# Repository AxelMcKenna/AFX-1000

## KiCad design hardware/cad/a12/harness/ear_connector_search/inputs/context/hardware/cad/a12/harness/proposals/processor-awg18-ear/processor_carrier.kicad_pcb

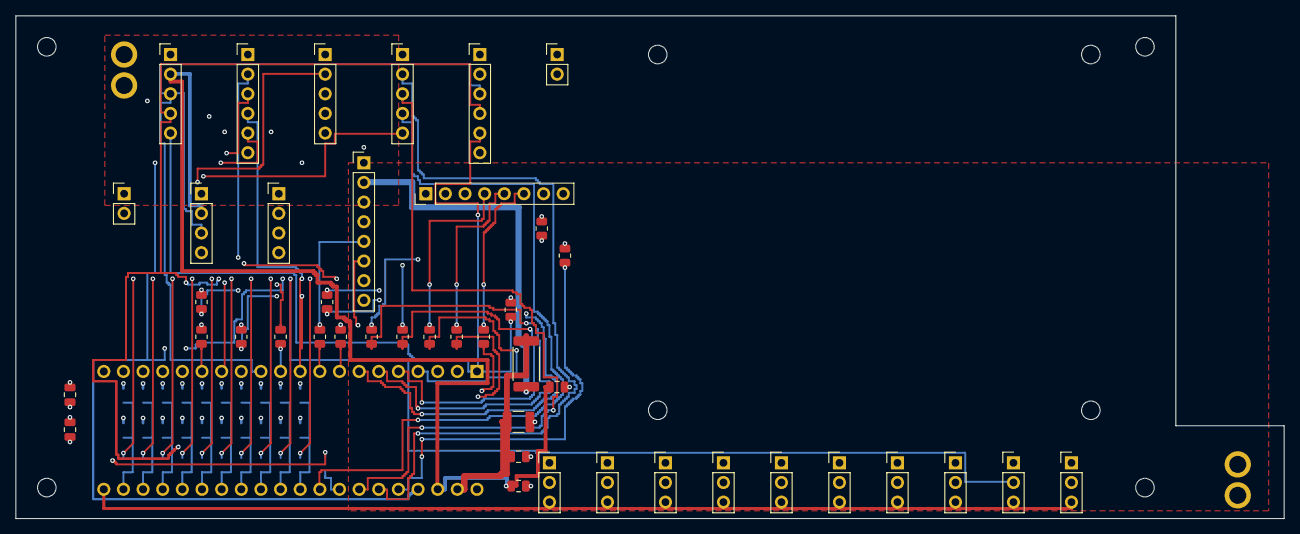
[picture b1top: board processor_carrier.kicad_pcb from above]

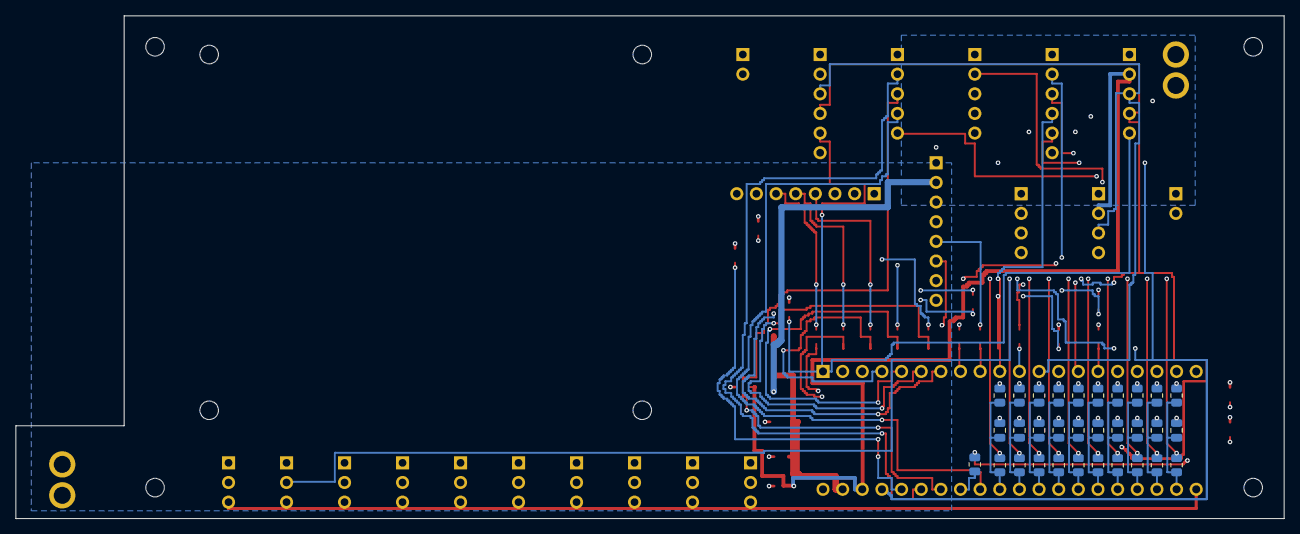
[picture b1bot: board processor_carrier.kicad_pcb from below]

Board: 4 copper layers, 164.0 x 65.0 mm, 85 parts (31 on the bottom side), 61 nets.

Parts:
C1: 22uF 25V X7R; C_1210_3225Metric
C2, C4, C6, C11, C12, C13, C14, C15, C16, C17, C18, C19, C20: 100nF 16V X7R; C_0805_2012Metric
C3: 1uF 16V X7R; C_0805_2012Metric
C5: 4.7uF 16V X7R; C_0805_2012Metric
H1, H2, H3, H4: M2_CLEARANCE; M2_Insert_Clearance
H5, H6, H7, H8: M2_CLEARANCE; M2_Daughter
J1, J13: Alpha6715_AWG18_DIRECT_SOLDER_PROPOSAL; AWG18_Solder_2x1_P4mm_D2p2
J2, J4, J5: Header5; PinHeader_1x05_P2.54mm_Vertical
J3, J6: Header6; PinHeader_1x06_P2.54mm_Vertical
J7, J8: Header2; PinHeader_1x02_P2.54mm_Vertical
J9, J10: Header4; PinHeader_1x04_P2.54mm_Vertical
J11, J12: Header8; PinHeader_1x08_P2.54mm_Vertical
J20, J21, J22, J23, J24, J25, J26, J27, J28, J29: Header3; PinHeader_1x03_P2.54mm_Vertical
R1: 0.47R 1% 1W; R_2512_6332Metric
R2: 10k 1%; R_0805_2012Metric
R3, R4, R5, R6: 100k 1%; R_0805_2012Metric
R10, R11, R12, R13, R14, R15, R16, R17, R18, R19, R20: 33R 1%; R_0805_2012Metric
R31, R32, R33, R34, R35, R36, R37, R38, R39, R40: 1k 1%; R_0805_2012Metric
R41, R42, R43, R44, R45, R46, R47, R48, R49, R50: 1M 1%; R_0805_2012Metric
U1: DaisySeed3; Seed3_Socket40

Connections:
/5V_DIG: J1.1, J11.2, J13.1, R1.1
/ADC_DATA: J5.4, U1.32
/AGND: C1.2, C2.2, C3.2, C4.2, C5.2, C6.2, C11.2, C12.2, C13.2, C14.2, C15.2, C16.2, C17.2, C18.2, C19.2, C20.2, J1.2, J2.1, J3.1, J4.1, J5.1, J6.1, J7.1, J8.1, J9.1, J10.1, J11.1, J11.8, J12.1, J13.2, J20.1, J21.1, J22.1, J23.1, J24.1, J25.1, J26.1, J27.1, J28.1, J29.1, R3.2, R4.2, R5.2, R6.2, R41.2, R42.2, R43.2, R44.2, R45.2, R46.2, R47.2, R48.2, R49.2, R50.2, U1.20, U1.40
/ANALOG_OK: J4.4, J6.6
/ARMED: J3.5, R5.1, U1.37
/BCLK: J5.2, U1.35
/BYPASS_SENSE: J3.6, J4.3
/CODEC_RUN: J2.5, J6.5, R6.1, U1.1
/DAC_DATA: J5.5, R14.2
/DAC_DATA_SRC: R14.1, U1.33
/GAIN_REQ: J3.4, R4.1, U1.10
/HEARTBEAT: J3.2, U1.14
/INPUT_READY: J4.5, J7.2
/LED_BLANK: J11.7, R2.1, R13.2
/LED_BLANK_SRC: R13.1, U1.15
/LED_MOSI: J11.4, R12.2
/LED_MOSI_SRC: R12.1, U1.11
/LED_SCK: J11.5, R11.2
/LED_SCK_SRC: R11.1, U1.9
/LED_XLAT: J11.6, R10.2
/LED_XLAT_SRC: R10.1, U1.8
/MCU_PERMIT: J3.3, R3.1, U1.36
/MODE_SEND_RETURN: J4.2, J8.2
/POT_ADC_00: C11.1, R31.2, R41.1, U1.22
/POT_ADC_01: C12.1, R32.2, R42.1, U1.23
/POT_ADC_02: C13.1, R33.2, R43.1, U1.24
/POT_ADC_03: C14.1, R34.2, R44.1, U1.25
/POT_ADC_04: C15.1, R35.2, R45.1, U1.26
/POT_ADC_05: C16.1, R36.2, R46.1, U1.27
/POT_ADC_06: C17.1, R37.2, R47.1, U1.28
/POT_ADC_07: C18.1, R38.2, R48.1, U1.29
/POT_ADC_08: C19.1, R39.2, R49.1, U1.30
/POT_ADC_09: C20.1, R40.2, R50.1, U1.31
/POT_RAW_00: J20.2, R31.1
/POT_RAW_01: J21.2, R32.1
/POT_RAW_02: J22.2, R33.1
/POT_RAW_03: J23.2, R34.1
/POT_RAW_04: J24.2, R35.1
/POT_RAW_05: J25.2, R36.1
/POT_RAW_06: J26.2, R37.1
/POT_RAW_07: J27.2, R38.1
/POT_RAW_08: J28.2, R39.1
/POT_RAW_09: J29.2, R40.1
/SCL: J2.3, J6.3, J9.3, J10.3, U1.12
/SDA: J2.4, J6.4, J9.4, J10.4, U1.13
/SDMMC_CLK: J12.8, R20.2
/SDMMC_CLK_SRC: R20.1, U1.7
/SDMMC_CMD: J12.7, R19.2
/SDMMC_CMD_SRC: R19.1, U1.6
/SDMMC_D0: J12.3, R15.2
/SDMMC_D0_SRC: R15.1, U1.5
/SDMMC_D1: J12.4, R16.2
/SDMMC_D1_SRC: R16.1, U1.4
/SDMMC_D2: J12.5, R17.2
/SDMMC_D2_SRC: R17.1, U1.3
/SDMMC_D3: J12.6, R18.2
/SDMMC_D3_SRC: R18.1, U1.2
/SEED_VIN: C1.1, C2.1, R1.2, U1.39
/V3V3_ANALOG: C3.1, C4.1, J20.3, J21.3, J22.3, J23.3, J24.3, J25.3, J26.3, J27.3, J28.3, J29.3, U1.21
/V3V3_IO: C5.1, C6.1, J2.2, J6.2, J9.2, J10.2, J11.3, J12.2, R2.2, U1.38
/WS: J5.3, U1.34

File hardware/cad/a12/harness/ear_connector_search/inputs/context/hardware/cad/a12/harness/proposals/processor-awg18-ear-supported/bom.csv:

Reference,Part_or_value,Footprint,Source,Note
U1,DaisySeed3,RMX_Carrier:Seed3_Socket40,https://daisy.nyc3.cdn.digitaloceanspaces.com/products/seed3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,External firmware profile only. Carrier assembly includes Seed3 and2xSSW-120-02-G-S sockets; clip socket solder tails<=3mm including solder.
J1,Alpha6715_AWG18_DIRECT_SOLDER_PROPOSAL,RMX_Carrier:AWG18_Solder_2x1_P4mm_D2p2,https://www.alphawire.com/products/wire/ecogen/ecowire/6715,"Separate direct-solder geometry proposal; max pretinned OD1.4mm, finished bores2.1..2.3mm, solder/strain/current/life unqualified"
J2,Header5,Connector_PinHeader_2.54mm:PinHeader_1x05_P2.54mm_Vertical,,E18 J5; CODEC_RUN alias CONTROL_RESET_N; external profile only.
J3,Header6,Connector_PinHeader_2.54mm:PinHeader_1x06_P2.54mm_Vertical,,E11 J2 six-pin order; bypass sense passes to E18 rear header.
J4,Header5,Connector_PinHeader_2.54mm:PinHeader_1x05_P2.54mm_Vertical,,E18 J4; BYPASS_SENSE alias MANUAL_BYPASS.
J5,Header5,Connector_PinHeader_2.54mm:PinHeader_1x05_P2.54mm_Vertical,,E09 J3; DAC_DATA source damping at carrier.
J6,Header6,Connector_PinHeader_2.54mm:PinHeader_1x06_P2.54mm_Vertical,,Split harness to E09 J4 IO power/J5 bus/status. Do not join independent3.3V outputs.
J7,Header2,Connector_PinHeader_2.54mm:PinHeader_1x02_P2.54mm_Vertical,,E11 J6 status.
J8,Header2,Connector_PinHeader_2.54mm:PinHeader_1x02_P2.54mm_Vertical,,Rear maintained CONNECTION contact: closed=send/return.
J9,Header4,Connector_PinHeader_2.54mm:PinHeader_1x04_P2.54mm_Vertical,,Trill Craft bus; include module pull-ups in whole-bus budget.
J10,Header4,Connector_PinHeader_2.54mm:PinHeader_1x04_P2.54mm_Vertical,,AS5600 board bus; sensor board incomplete.
J11,Header8,Connector_PinHeader_2.54mm:PinHeader_1x08_P2.54mm_Vertical,,TLC5947 board interface; receiving BLANK pull-up still required on future LED board.
J12,Header8,Connector_PinHeader_2.54mm:PinHeader_1x08_P2.54mm_Vertical,,"Reserved SDMMC interface. Card-power budget, socket/detect, filesystem and physical SI unfinished."
R1,0.47R 1% 1W,Resistor_SMD:R_2512_6332Metric,,"Source resistor budget uses0.5A; physical load, thermal and startup qualification open."
R2,10k 1%,Resistor_SMD:R_0805_2012Metric,,
R3,100k 1%,Resistor_SMD:R_0805_2012Metric,,
R4,100k 1%,Resistor_SMD:R_0805_2012Metric,,
R5,100k 1%,Resistor_SMD:R_0805_2012Metric,,
R6,100k 1%,Resistor_SMD:R_0805_2012Metric,,
R10,33R 1%,Resistor_SMD:R_0805_2012Metric,,Source damping; physical edge/SI qualification unfinished.
R11,33R 1%,Resistor_SMD:R_0805_2012Metric,,Source damping; physical edge/SI qualification unfinished.
R12,33R 1%,Resistor_SMD:R_0805_2012Metric,,Source damping; physical edge/SI qualification unfinished.
R13,33R 1%,Resistor_SMD:R_0805_2012Metric,,Source damping; physical edge/SI qualification unfinished.
R14,33R 1%,Resistor_SMD:R_0805_2012Metric,,Source damping; physical edge/SI qualification unfinished.
R15,33R 1%,Resistor_SMD:R_0805_2012Metric,,Source damping; physical edge/SI qualification unfinished.
R16,33R 1%,Resistor_SMD:R_0805_2012Metric,,Source damping; physical edge/SI qualification unfinished.
R17,33R 1%,Resistor_SMD:R_0805_2012Metric,,Source damping; physical edge/SI qualification unfinished.
R18,33R 1%,Resistor_SMD:R_0805_2012Metric,,Source damping; physical edge/SI qualification unfinished.
R19,33R 1%,Resistor_SMD:R_0805_2012Metric,,Source damping; physical edge/SI qualification unfinished.
R20,33R 1%,Resistor_SMD:R_0805_2012Metric,,Source damping; physical edge/SI qualification unfinished.
C1,22uF 25V X7R,Capacitor_SMD:C_1210_3225Metric,,
C2,100nF 16V X7R,Capacitor_SMD:C_0805_2012Metric,,
C3,1uF 16V X7R,Capacitor_SMD:C_0805_2012Metric,,
C4,100nF 16V X7R,Capacitor_SMD:C_0805_2012Metric,,
C5,4.7uF 16V X7R,Capacitor_SMD:C_0805_2012Metric,,
C6,100nF 16V X7R,Capacitor_SMD:C_0805_2012Metric,,
J20,Header3,Connector_PinHeader_2.54mm:PinHeader_1x03_P2.54mm_Vertical,,input: 10k linear pot; excitation is module analog3.3V output.
R31,1k 1%,Resistor_SMD:R_0805_2012Metric,,
C11,100nF 16V X7R,Capacitor_SMD:C_0805_2012Metric,,
R41,1M 1%,Resistor_SMD:R_0805_2012Metric,,Open-wiper bleed; does not provide wire-fault detection.
J21,Header3,Connector_PinHeader_2.54mm:PinHeader_1x03_P2.54mm_Vertical,,output: 10k linear pot; excitation is module analog3.3V output.
R32,1k 1%,Resistor_SMD:R_0805_2012Metric,,
C12,100nF 16V X7R,Capacitor_SMD:C_0805_2012Metric,,
R42,1M 1%,Resistor_SMD:R_0805_2012Metric,,Open-wiper bleed; does not provide wire-fault detection.
J22,Header3,Connector_PinHeader_2.54mm:PinHeader_1x03_P2.54mm_Vertical,,low: 10k linear pot; excitation is module analog3.3V output.
R33,1k 1%,Resistor_SMD:R_0805_2012Metric,,
C13,100nF 16V X7R,Capacitor_SMD:C_0805_2012Metric,,
R43,1M 1%,Resistor_SMD:R_0805_2012Metric,,Open-wiper bleed; does not provide wire-fault detection.
J23,Header3,Connector_PinHeader_2.54mm:PinHeader_1x03_P2.54mm_Vertical,,mid: 10k linear pot; excitation is module analog3.3V output.
R34,1k 1%,Resistor_SMD:R_0805_2012Metric,,
C14,100nF 16V X7R,Capacitor_SMD:C_0805_2012Metric,,
R44,1M 1%,Resistor_SMD:R_0805_2012Metric,,Open-wiper bleed; does not provide wire-fault detection.
J24,Header3,Connector_PinHeader_2.54mm:PinHeader_1x03_P2.54mm_Vertical,,high: 10k linear pot; excitation is module analog3.3V output.
R35,1k 1%,Resistor_SMD:R_0805_2012Metric,,
C15,100nF 16V X7R,Capacitor_SMD:C_0805_2012Metric,,
R45,1M 1%,Resistor_SMD:R_0805_2012Metric,,Open-wiper bleed; does not provide wire-fault detection.
J25,Header3,Connector_PinHeader_2.54mm:PinHeader_1x03_P2.54mm_Vertical,,scene_depth: 10k linear pot; excitation is module analog3.3V output.
R36,1k 1%,Resistor_SMD:R_0805_2012Metric,,
C16,100nF 16V X7R,Capacitor_SMD:C_0805_2012Metric,,
R46,1M 1%,Resistor_SMD:R_0805_2012Metric,,Open-wiper bleed; does not provide wire-fault detection.
J26,Header3,Connector_PinHeader_2.54mm:PinHeader_1x03_P2.54mm_Vertical,,x_level: 10k linear pot; excitation is module analog3.3V output.
R37,1k 1%,Resistor_SMD:R_0805_2012Metric,,
C17,100nF 16V X7R,Capacitor_SMD:C_0805_2012Metric,,
R47,1M 1%,Resistor_SMD:R_0805_2012Metric,,Open-wiper bleed; does not provide wire-fault detection.
J27,Header3,Connector_PinHeader_2.54mm:PinHeader_1x03_P2.54mm_Vertical,,x_pitch: 10k linear pot; excitation is module analog3.3V output.
R38,1k 1%,Resistor_SMD:R_0805_2012Metric,,
C18,100nF 16V X7R,Capacitor_SMD:C_0805_2012Metric,,
R48,1M 1%,Resistor_SMD:R_0805_2012Metric,,Open-wiper bleed; does not provide wire-fault detection.
J28,Header3,Connector_PinHeader_2.54mm:PinHeader_1x03_P2.54mm_Vertical,,scene_time: 10k linear pot; excitation is module analog3.3V output.
R39,1k 1%,Resistor_SMD:R_0805_2012Metric,,
C19,100nF 16V X7R,Capacitor_SMD:C_0805_2012Metric,,
R49,1M 1%,Resistor_SMD:R_0805_2012Metric,,Open-wiper bleed; does not provide wire-fault detection.
J29,Header3,Connector_PinHeader_2.54mm:PinHeader_1x03_P2.54mm_Vertical,,scene_resonance: 10k linear pot; excitation is module analog3.3V output.
R40,1k 1%,Resistor_SMD:R_0805_2012Metric,,
C20,100nF 16V X7R,Capacitor_SMD:C_0805_2012Metric,,
R50,1M 1%,Resistor_SMD:R_0805_2012Metric,,Open-wiper bleed; does not provide wire-fault detection.
J13,Alpha6715_AWG18_DIRECT_SOLDER_PROPOSAL,RMX_Carrier:AWG18_Solder_2x1_P4mm_D2p2,https://www.alphawire.com/products/wire/ecogen/ecowire/6715,"Private ear input force pads; shared2.4A input target, all branch/PDN/assembly/strain/contact/fit qualification pending. Original J1 wire is unfitted service access."

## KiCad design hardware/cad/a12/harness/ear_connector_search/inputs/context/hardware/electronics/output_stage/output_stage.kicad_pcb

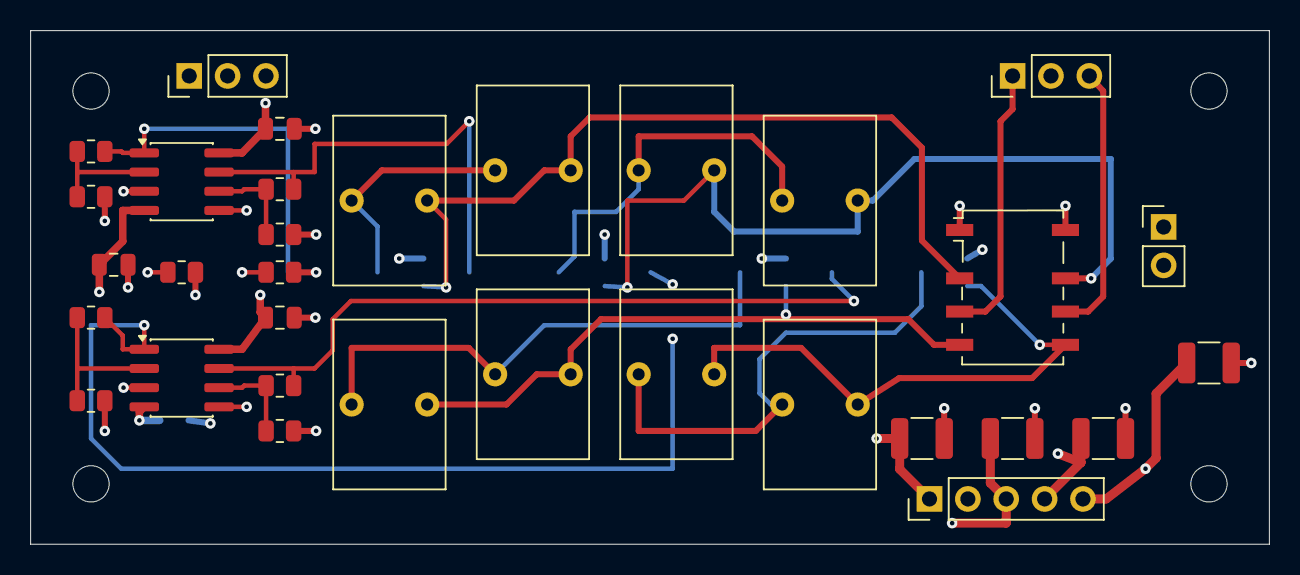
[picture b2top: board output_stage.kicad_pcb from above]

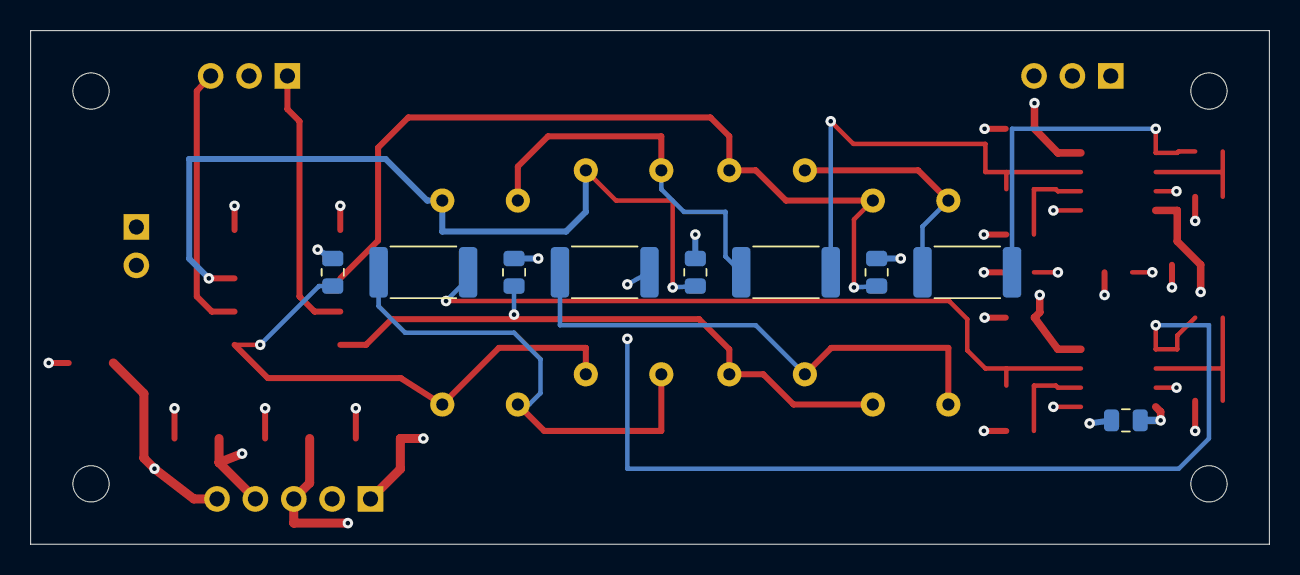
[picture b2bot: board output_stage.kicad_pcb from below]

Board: 4 copper layers, 82.0 x 34.0 mm, 45 parts (9 on the bottom side), 27 nets.

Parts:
C1, C2, C3, C4, C13, C14, C15, C16: 4.7uF film 63V 10%; C_Rect_L7.2mm_W11.0mm_P5.00mm_FKS2_FKP2_MKS2_MKP2
C5, C6, C7, C8: 100nF 50V X7R; C_0805_2012Metric
C9, C10, C11, C12: 10uF 50V X7R; C_1210_3225Metric
H1, H2, H3, H4: M2_CLEARANCE; M2_Insert_Clearance
J1: POST_RECEIVER; PinHeader_1x03_P2.54mm_Vertical
J2: E03_PROCESSED_OUT; PinHeader_1x03_P2.54mm_Vertical
J3: E02_J5_GAIN_COIL; PinHeader_1x02_P2.54mm_Vertical
J4: REGULATED_RAILS; PinHeader_1x05_P2.54mm_Vertical
K3: G6K-2F-Y DC5; Relay_DPDT_Omron_G6K-2F-Y
R1, R5: 5.23k 0.1%; R_0805_2012Metric
R2, R6: 1k 0.1%; R_0805_2012Metric
R3, R7, R11, R15: 100 1% 1W; R_2512_6332Metric
R4, R8, R12, R16: 20k 1%; R_0805_2012Metric
R9, R13: 1.21k 0.1%; R_0805_2012Metric
R10, R14: 2k 0.1%; R_0805_2012Metric
R17, R18: 100k 1%; R_0805_2012Metric
U1: OPA2992D; SOIC-8_3.9x4.9mm_P1.27mm
U2: OPA1612AID; SOIC-8_3.9x4.9mm_P1.27mm

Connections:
/5V: J3.1, K3.1
/AGND: C5.2, C6.2, C7.2, C8.2, C9.2, C10.2, C11.2, C12.2, J1.2, J2.2, J4.2, R2.2, R4.2, R6.2, R8.2, R10.2, R12.2, R14.2, R16.2, R17.2, R18.2
/GAIN_LOW: J3.2, K3.8
/M_AC_L: C1.2, C13.2, K3.2, R4.1
/M_AC_R: C2.2, C14.2, K3.7, R8.1
/M_DRV_L: R1.2, R3.1, U1.1
/M_DRV_R: R5.2, R7.1, U1.7
/M_FB_L: R1.1, R2.1, U1.2
/M_FB_R: R5.1, R6.1, U1.6
/M_SER_L: C1.1, C13.1, R3.2
/M_SER_R: C2.1, C14.1, R7.2
/N12: C8.1, C12.1, J4.5, U2.4
/N19: C6.1, C10.1, J4.3, U1.4
/P12: C7.1, C11.1, J4.4, U2.8
/P19: C5.1, C9.1, J4.1, U1.8
/PROC_OUT_L: J2.1, K3.3
/PROC_OUT_R: J2.3, K3.6
/RECV_L: J1.1, R17.1, U1.3, U2.3
/RECV_R: J1.3, R18.1, U1.5, U2.5
/S_AC_L: C3.2, C15.2, K3.4, R12.1
/S_AC_R: C4.2, C16.2, K3.5, R16.1
/S_DRV_L: R9.2, R11.1, U2.1
/S_DRV_R: R13.2, R15.1, U2.7
/S_FB_L: R9.1, R10.1, U2.2
/S_FB_R: R13.1, R14.1, U2.6
/S_SER_L: C3.1, C15.1, R11.2
/S_SER_R: C4.1, C16.1, R15.2

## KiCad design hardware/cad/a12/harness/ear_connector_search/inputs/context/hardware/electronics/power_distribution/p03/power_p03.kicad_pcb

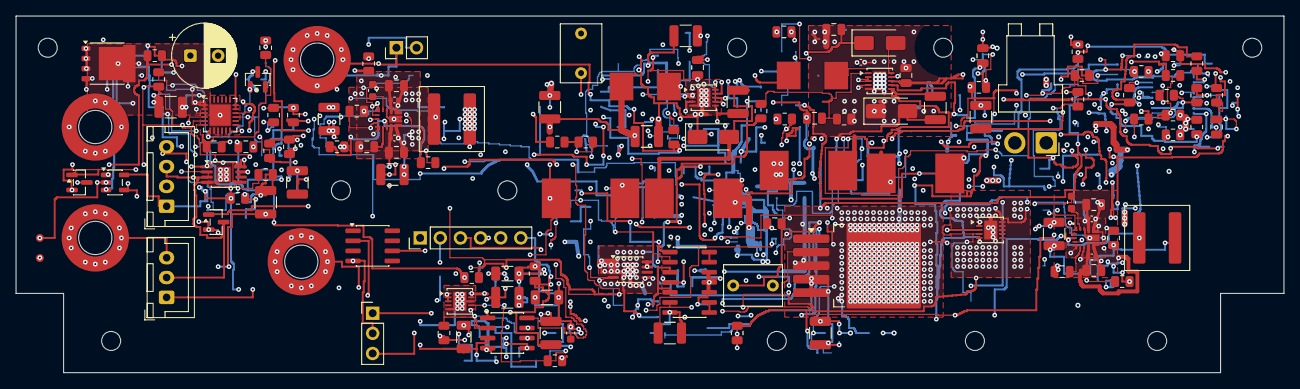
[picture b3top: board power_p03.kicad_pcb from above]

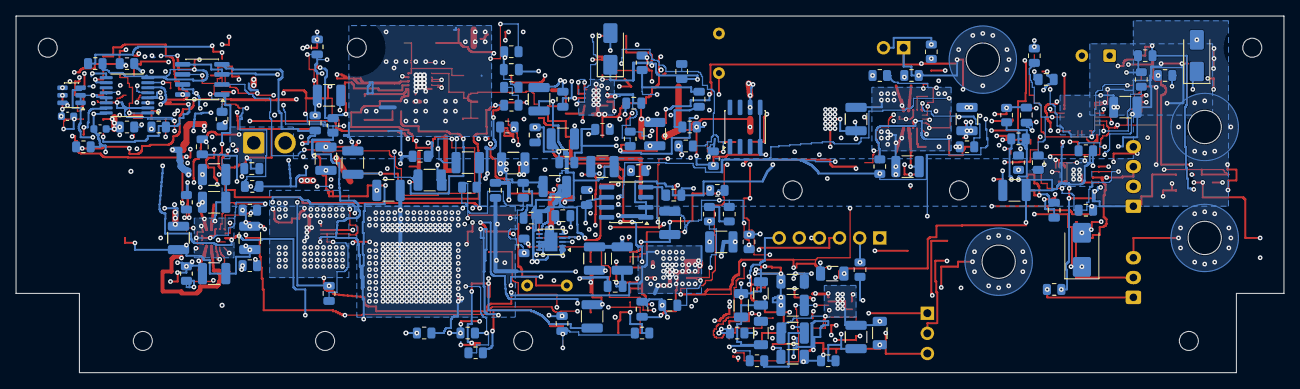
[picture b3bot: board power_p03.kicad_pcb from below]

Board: 6 copper layers, 160.0 x 45.0 mm, 265 parts (127 on the bottom side), 108 nets.

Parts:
C1, C63: 10uF 63V X7R; C_1210_3225Metric
C2, C3, C5, C6, C8, C9, C37, C42, C52, C57, C64, C65, C67, C68, C70, C204, C205, C224, C225, C254: 22uF 50V X7R 20% TDK C3225X7R1H226M250AC; C_1210_3225Metric
C4, C7, C10, C35, C38, C40, C43, C50, C53, C55, C58, C59, C61, C66, C69, C71: 100nF 50V X7R; C_0805_2012Metric
C11, C30, C107, C108: 100nF 16V X7R; C_0805_2012Metric
C12, C14, C73, C75: 68pF 50V C0G 5%; C_0805_2012Metric
C13, C15, C74, C76: 330nF 16V X7R; C_0805_2012Metric
C31: 2.2uF 16V X7R; C_0805_2012Metric
C32, C33: 1uF film 63V 10% MKS2C041001F00KSSD; C_Rect_L7.2mm_W5.0mm_P5.00mm
C34, C39, C49, C54, C240: 47nF 50V C0G 5%; C_1210_3225Metric
C36, C41, C51, C56: 10uF 50V X7R; C_1210_3225Metric
C60, C62, C105: 1uF 50V X7R; C_0805_2012Metric
C72, C210, C211, C230, C231: 100nF 50V X7R 10% TDK C1005X7R1H104K050BB; C_0402_1005Metric
C101, C102: 2.2uF 100V X7R; C_1210_3225Metric
C103: 220uF 35V electrolytic 20% (EEUFR1V221); CP_Radial_D8.0mm_P3.50mm
C104: 1uF 50V X7R; C_1210_3225Metric
C106: 10uF 16V X7R; C_1210_3225Metric
C109: 1nF 16V C0G 5%; C_0805_2012Metric
C110: 10nF 16V C0G 5%; C_0805_2012Metric
C200, C220: 4.7uF 25V X7R 10% TDK C2012X7R1E475K125AB; C_0805_2012Metric
C201, C221, C255, C301, C302: 100nF 50V X7R; C_0603_1608Metric
C202, C203, C222, C223: 2.2uF 50V X7R 10% TDK C2012X7R1H225K125AC; C_0805_2012Metric
C206, C207, C208, C209, C226, C227, C228, C229: 47uF 25V X7S 20% TDK C3225X7S1E476M250AC; C_1210_3225Metric
C241: 1uF 25V X7R; C_1210_3225Metric
C242, C243, C244, C245, C246, C247, C248, C249, C250, C251: 100nF 25V C0G 5% KEMET C1206C104J3GACTU; C_1206_3216Metric
C252, C253: 1uF 16V X7R; C_1210_3225Metric
C300: 10nF 50V C0G 5%; C_0805_2012Metric
D1, D2, D3, D4, D103: SS16-E3/61T; D_SMA
D101: SMBJ33CA-E3/52; D_SMB
D102: BAS116,215; SOT-23
H1, H2, H3, H4, H5, H6, H7, H8, H9, H10: M2_CLEARANCE; M2_Clearance
J2: Header6; PinHeader_1x06_P2.54mm_Vertical
J3: Header2; PinHeader_1x02_P2.54mm_Vertical
J20, J21, J23, J24: Wurth 7466003R M3 SMT; Wurth_7466003R
J22: P03 READY test; PinHeader_1x03_P2.54mm_Vertical
J101: JST B2PS-VH (VHR-2N/SVH-41T-P1.1 AWG16); JST_VH_B2PS-VH_1x02_P3.96mm_Horizontal
J103: Bare POWER_READY probe pads, no fitted header; Probe2_P2.54_D1
J104: JST B3B-XH-A (XHP-3/SXH-001T-P0.6); JST_XH_B3B-XH-A_1x03_P2.50mm_Vertical
J106: JST B4B-XH-A (XHP-4/SXH-001T-P0.6); JST_XH_B4B-XH-A_1x04_P2.50mm_Vertical
L1, L6: 33uH 20% SRP7050WA-330M; SRP7050WA
L2, L3, L7, L8: 68uH 20% SRP1050WA-680M; SRP1050WA
L20, L23: 4.7uH 20% Coilcraft XAL7030-472MEC; L_Coilcraft_XAL7030-472
Q101: PSMN012-100YL,115; LFPAK56
Q102: BSS138-7-F; SOT-23
Q103: DMN2056U-7; SOT-23
R1: 300k 0.01% 5ppm; R_0805_2012Metric
R2, R3, R4, R45, R46: 15k 0.01% 5ppm; R_0805_2012Metric
R5, R20, R21, R34, R35: 330k 0.01% 5ppm; R_0805_2012Metric
R6, R7, R49, R50: 4.7k 1%; R_0805_2012Metric
R17, R19, R110: 1k 1%; R_0805_2012Metric
R18, R120: 100k 1%; R_0805_2012Metric
R22, R27, R36, R41, R243, R244: 100k 0.01% 5ppm; R_0805_2012Metric
R23, R28, R37, R42, R241: 6.8k 1%; R_0805_2012Metric
R24, R38: 9.09k 1%; R_0805_2012Metric
R25, R39, R47, R306: 200k 0.01% 5ppm; R_0805_2012Metric
R26, R40, R308: 180k 0.01% 5ppm; R_0805_2012Metric
R29, R43: 5.62k 1%; R_0805_2012Metric
R44: 240k 0.01% 5ppm; R_0805_2012Metric
R48, R301, R303, R305, R307, R309, R314: 10k 0.01% 5ppm; R_0805_2012Metric
R101, R103, R117: 309k 0.1% 10ppm; R_0805_2012Metric
R102: 40.2k 0.1% 10ppm; R_0805_2012Metric
R104: 28k 0.1% 10ppm; R_0805_2012Metric
R105: 68.1k 0.1% 10ppm; R_0805_2012Metric
R106, R109, R118, R119: 10k 0.1% 10ppm; R_0805_2012Metric
R107: 4.02k 0.1% 10ppm; R_0805_2012Metric
R108: 11.7k 0.1% 10ppm; R_0805_2012Metric
R111, R204, R224, R246: 10k 1%; R_0805_2012Metric
R112, R114: 47k 1%; R_0805_2012Metric
R113: 3.3k 1%; R_0805_2012Metric
R115: 30.9k 0.1% 10ppm; R_0805_2012Metric
R116: 3.09k 0.1% 10ppm; R_0805_2012Metric
R121: 100 1%; R_0805_2012Metric
R130: 49.9 0.01% 5ppm; R_0805_2012Metric
R200: 9k 0.01% 2ppm Susumu RG2012L-902-L-T1; R_0805_2012Metric
R201: 1k 0.01% 2ppm Susumu RG2012L-102-L-T1; R_0805_2012Metric
R202, R222: 24.3k 1%; R_0805_2012Metric
R203, R223: 18.2k 0.1% 25ppm Panasonic ERA6AEB1822V; R_0805_2012Metric
R205, R225: 22k 1%; R_0805_2012Metric
R206: 54.9 0.1% 25ppm Panasonic ERA6AEB549V; R_0805_2012Metric
R220: 11k 0.01% 5ppm; R_0805_2012Metric
R221, R311: 1k 0.01% 5ppm; R_0805_2012Metric
R240: 100 0.01% 5ppm; R_0805_2012Metric
R242: 120 0.01% 5ppm; R_0805_2012Metric
R245: 2.21k 1%; R_0805_2012Metric
R300, R302: 87.6k 0.01% 5ppm; R_0805_2012Metric
R304: 324k 0.01% 5ppm; R_0805_2012Metric
R310: 590 0.01% 5ppm; R_0805_2012Metric
R312: 7.5k 0.01% 5ppm; R_0805_2012Metric
R313: 1M 0.01% 5ppm; R_0805_2012Metric
R315: 750k 0.01% 5ppm; R_0805_2012Metric
R316: 2.2k 0.1% 25ppm Panasonic ERA6AEB222V; R_0805_2012Metric
U1, U13: LT3471EDD#PBF; DFN-10-1EP_3x3mm_P0.5mm_EP1.65x2.38mm
U4: REF5025EIDR; SOIC-8_3.9x4.9mm_P1.27mm
U5: OPA4192ID; SOIC-14_3.9x8.7mm_P1.27mm
U6, U24: OPA2192ID; SOIC-8_3.9x4.9mm_P1.27mm
U7: LT3080IMS8E#PBF; MSOP-8-1EP_3x3mm_P0.65mm_EP1.68x1.88mm
U8: LT3080IQ#PBF; TO-263-5_TabPin3
U10, U11: LT3090IDD#PBF; DFN-10-1EP_3x3mm_P0.5mm_EP1.65x2.38mm
U12: LT1634AIS8-2.5#PBF; SOIC-8_3.9x4.9mm_P1.27mm
U20, U23: TPS543620RPYR; TPS543620_RPY0014A
U21: ADR4550BRZ; SOIC-8_3.9x4.9mm_P1.27mm
U22: LT3045IDD#PBF; DFN-10-1EP_3x3mm_P0.5mm_EP1.65x2.38mm
U25: LTC2910HGN#PBF; SSOP-16_3.9x4.9mm_P0.635mm
U26: SN74LVC1G97DBVR; SOT-23-6
U101: TPS26630RGER; Texas_RGE0024H_VQFN-24-1EP_4x4mm_P0.5mm_EP2.7x2.7mm
U102: TPS7A1601DGNR; MSOP-8-1EP_3x3mm_P0.65mm_EP1.68x1.88mm
U103: TLV7011DBVR; SOT-23-5

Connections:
/5V_DIG_SRC: C30.1, C206.1, C207.1, C208.1, C209.1, J3.1, J23.1, L20.2, R6.1, R7.1, R49.1, R50.1, R200.1, R300.1, U4.1, U4.2, U10.5, U11.5
/AGND: C2.2, C3.2, C4.2, C5.2, C6.2, C7.2, C8.2, C9.2, C10.2, C11.2, C13.2, C15.2, C30.2, C31.2, C32.2, C33.2, C35.2, C36.2, C37.2, C38.2, C40.2, C41.2, C42.2, C43.2, C50.2, C51.2, C52.2, C53.2, C55.2, C56.2, C57.2, C58.2, C59.2, C60.2, C61.2, C62.2, C64.2, C65.2, C66.2, C67.2, C68.2, C69.2, C70.2, C71.2, C72.2, C74.2, C76.2, C101.2, C102.2, C103.2, C104.2, C105.2, C106.2, C107.2, C108.2, C109.2, C110.2, C200.2, C202.2, C203.2, C204.2, C205.2, C206.2, C207.2, C208.2, C209.2, C210.2, C211.2, C220.2, C222.2, C223.2, C224.2, C225.2, C226.2, C227.2, C228.2, C229.2, C230.2, C231.2, C241.2, C242.2, C243.2, C244.2, C245.2, C246.2, C247.2, C248.2, C249.2, C250.2, C251.2, C252.2, C253.2, C254.2, C255.2, C300.2, C301.2, C302.2, D2.1, D4.1, D101.2, D103.2, J2.2, J3.2, J20.1, J21.1, J22.2, J101.2, J103.1, J104.3, J106.2, Q103.2, R3.2, R22.2, R24.2, R27.2, R29.2, R36.2, R38.2, R41.2, R43.2, R45.2, R102.2, R104.2, R106.2, R107.2, R109.2, R111.2, R112.2, R114.2, R116.2, R119.2, R120.2, R201.2, R202.2, R203.2, R205.2, R221.2, R222.2, R223.2, R225.2, R243.2, R245.2, R301.2, R303.2, R305.2, R307.2, R309.2, R311.2, U1.5, U1.11, U4.4, U5.10, U5.11, U5.12, U6.8, U10.3, U11.3, U12.6, U13.5, U13.11, U20.5, U20.9, U20.11, U21.4, U22.5, U22.8, U22.11, U23.5, U23.9, U23.11, U24.4, U24.5, U25.9, U25.13, U25.14, U26.1, U26.2, U101.8, U101.25, U102.4, U102.9, U103.2
/AUX_FB: R109.1, R130.2, U102.2
/AUX_START_DELAY: C110.1, U102.7
/BLOCK_DRV: Q102.1, U101.4
/BLOCK_GATE: Q101.4, Q102.3, U101.3
/CUK_NODE: C1.2, D2.2, L3.1
/DC_IN: C101.1, D101.1, J101.1, Q101.1, Q101.2, Q101.3, Q102.2, R101.1, R103.1, U101.5
/FAST_OV_GATE: Q103.1, R120.1, R121.2
/FAST_OV_OUT: R117.1, R121.1, U103.1
/FAST_OV_REF: C109.1, R118.2, R119.1, U103.4
/FAST_OV_SENSE: R115.2, R116.1, R117.2, U103.3
/INPUT_ILIM: R107.1, U101.10
/INPUT_OV: D102.1, R103.2, R104.1, U101.7
/INPUT_PGTH: R105.2, R106.1, U101.15
/INPUT_SLEW: C105.1, U101.9
/INPUT_UV: R101.2, R102.1, U101.6
/LO_CUK_NODE: C63.2, D4.2, L8.1
/LO_N_FB: C75.2, R46.2, R47.1, U13.4
/LO_N_RMID: R47.2, R48.1
/LO_N_SS: C76.1, R50.2, U13.7
/LO_N_SW: C63.1, L7.2, U13.6
/LO_P_FB: C73.2, R44.2, R45.1, U13.1
/LO_P_SS: C74.1, R49.2, U13.9
/LO_P_SW: D3.2, L6.2, U13.10
/LO_REF_1V: C72.1, R46.1, U13.2, U13.3
/N12_DRIVE: C54.1, R42.1, U6.7
/N12_FB: C54.2, R40.2, R41.1, U6.6
/N12_RMID: R39.2, R40.1
/N12_SET: C55.1, R39.1, R42.2, U11.4
/N12_SRC: C57.1, C58.1, J2.5, R43.1, R315.2, U11.1, U11.2
/N19_DRIVE: C49.1, R37.1, U6.1
/N19_FB: C49.2, R35.2, R36.1, U6.2
/N19_RMID: R34.2, R35.1
/N19_SET: C50.1, R34.1, R37.2, U10.4
/N19_SRC: C52.1, C53.1, J2.3, R38.1, R313.2, U10.1, U10.2
/NREF_2V5: R18.1, R19.1, U12.4, U12.5
/NREF_FILTER: C33.1, R19.2, U6.3, U6.5
/P03_ALL_SOURCES_READY: J22.1, J106.4, R316.2, U25.12
/P03_ANA_DIV: R242.2, R243.1, R244.1
/P03_ANA_DRIVE: C240.1, R241.1, U24.1
/P03_ANA_FB: C240.2, R244.2, U24.2
/P03_ANA_SET: C241.1, R241.2, R242.1, U22.7
/P03_AUX_TRIM: R108.2, R130.1
/P03_A_BOOT: C221.1, U23.14
/P03_A_BP5: C220.1, U23.6
/P03_A_ENABLE: R224.2, R225.1, U23.7
/P03_A_FB: R220.2, R221.1, U23.4
/P03_A_FSEL: R222.1, U23.1
/P03_A_MODE: R223.1, U23.2
/P03_A_SW: C221.2, L23.1, U23.10, U23.13
/P03_D_BOOT: C201.1, U20.14
/P03_D_BP5: C200.1, U20.6
/P03_D_ENABLE: R204.2, R205.1, U20.7
/P03_D_FB: R201.1, R206.2, U20.4
/P03_D_FB_TRIM: R200.2, R206.1
/P03_D_FSEL: R202.1, U20.1
/P03_D_MODE: R203.1, U20.2
/P03_D_SW: C201.2, L20.1, U20.10, U20.13
/P03_MON_ANA: R302.2, R303.1, U25.2
/P03_MON_BUCK_OK: U25.5, U26.4
/P03_MON_DIG: R300.2, R301.1, U25.1
/P03_MON_N12: R314.2, R315.1, U25.8
/P03_MON_N19: R312.2, R313.1, U25.7
/P03_MON_NEG_BIAS: R310.2, R311.1, R312.1, R314.1
/P03_MON_P12: R306.2, R307.1, U25.4
/P03_MON_P19: R304.2, R305.1, U25.3
/P03_MON_REF: R310.1, U25.10
/P03_MON_TIMER: C300.1, U25.15
/P03_MON_VIN: R308.2, R309.1, U25.6
/P03_PRE6V: C226.1, C227.1, C228.1, C229.1, C253.1, L23.2, R220.1, U21.2, U22.1, U22.2, U22.3, U22.6
/P03_REF5: C252.1, R240.1, U21.6
/P03_REF_FILTER: C242.1, C243.1, C244.1, C245.1, C246.1, C247.1, C248.1, C249.1, C250.1, C251.1, R240.2, U24.3
/P03_SOURCES_READY: R246.2, U20.3, U23.3, U26.3
/P03_SPARE_24: U24.6, U24.7
/P03_SPARE_C: U5.8, U5.9
/P12_DRIVE: C39.1, R28.1, U5.7
/P12_FB: C39.2, R26.2, R27.1, U5.6
/P12_RMID: R25.2, R26.1
/P12_SET: C40.1, R25.1, R28.2, U8.2
/P12_SRC: C42.1, C43.1, J2.4, R29.1, R306.1, U8.3
/P19_DRIVE: C34.1, R23.1, U5.1
/P19_FB: C34.2, R21.2, R22.1, U5.2
/P19_RMID: R20.2, R21.1
/P19_SET: C35.1, R20.1, R23.2, U7.4
/P19_SRC: C37.1, C38.1, J2.1, R24.1, R304.1, U7.1, U7.2, U7.3, U7.9
/POWER_READY: J22.3, J103.2, R110.2, R204.1, R224.1, U26.6, U101.16
/POWER_RUN: J104.2, J106.3, Q103.3, R112.1, U101.12, U102.3
/PREF_2V5: C31.1, R17.1, U4.6
/PREF_FILTER: C32.1, R17.2, U5.3, U5.5
/RAW_N17: C56.1, C67.1, C68.1, C69.1, C75.1, L8.2, R48.2, U11.8, U11.9, U11.10, U11.11
/RAW_N22: C8.1, C9.1, C10.1, C14.1, C51.1, C61.1, C62.1, L3.2, R5.2, R18.2, U6.4, U10.8, U10.9, U10.10, U10.11
/RAW_N_FB: C14.2, R4.2, R5.1, U1.4
/RAW_N_SS: C15.1, R7.2, U1.7
/RAW_N_SW: C1.1, L2.2, U1.6
/RAW_P17: C41.1, C64.1, C65.1, C66.1, C73.1, D3.1, R44.1, U8.4, U8.5
/RAW_P22: C5.1, C6.1, C7.1, C12.1, C36.1, C59.1, C60.1, D1.1, R1.1, U5.4, U7.5, U7.7, U7.8
/RAW_P_FB: C12.2, R2.2, R3.1, U1.1
/RAW_P_RMID: R1.2, R2.1
/RAW_P_SS: C13.1, R6.2, U1.9
/RAW_P_SW: D1.2, L1.2, U1.10
/SPARE_OUT: U5.13, U5.14
/SWITCH_SUPPLY: J104.1, R113.2
/SW_REF_1V: C11.1, R4.1, U1.2, U1.3
/V2V5_AUX: C106.1, C107.1, C108.1, C301.1, C302.1, D102.3, J106.1, R108.1, R110.1, R111.1, R113.1, R118.1, R246.1, R316.1, U25.16, U26.5, U102.1, U103.5
/V5_REG_SRC: C254.1, J2.6, J24.1, R245.1, R302.1, U22.9, U22.10
/VIN_IC: C102.1, Q101.5, R115.1, U101.1, U101.2, U102.5, U102.8
/VIN_PROTECTED: C2.1, C3.1, C4.1, C70.1, C71.1, C103.1, C104.1, C202.1, C203.1, C204.1, C205.1, C210.1, C211.1, C222.1, C223.1, C224.1, C225.1, C230.1, C231.1, C255.1, D103.1, L1.1, L2.1, L6.1, L7.1, R105.1, R114.1, R308.1, U1.8, U13.8, U20.8, U20.12, U23.8, U23.12, U24.8, U101.17, U101.18
